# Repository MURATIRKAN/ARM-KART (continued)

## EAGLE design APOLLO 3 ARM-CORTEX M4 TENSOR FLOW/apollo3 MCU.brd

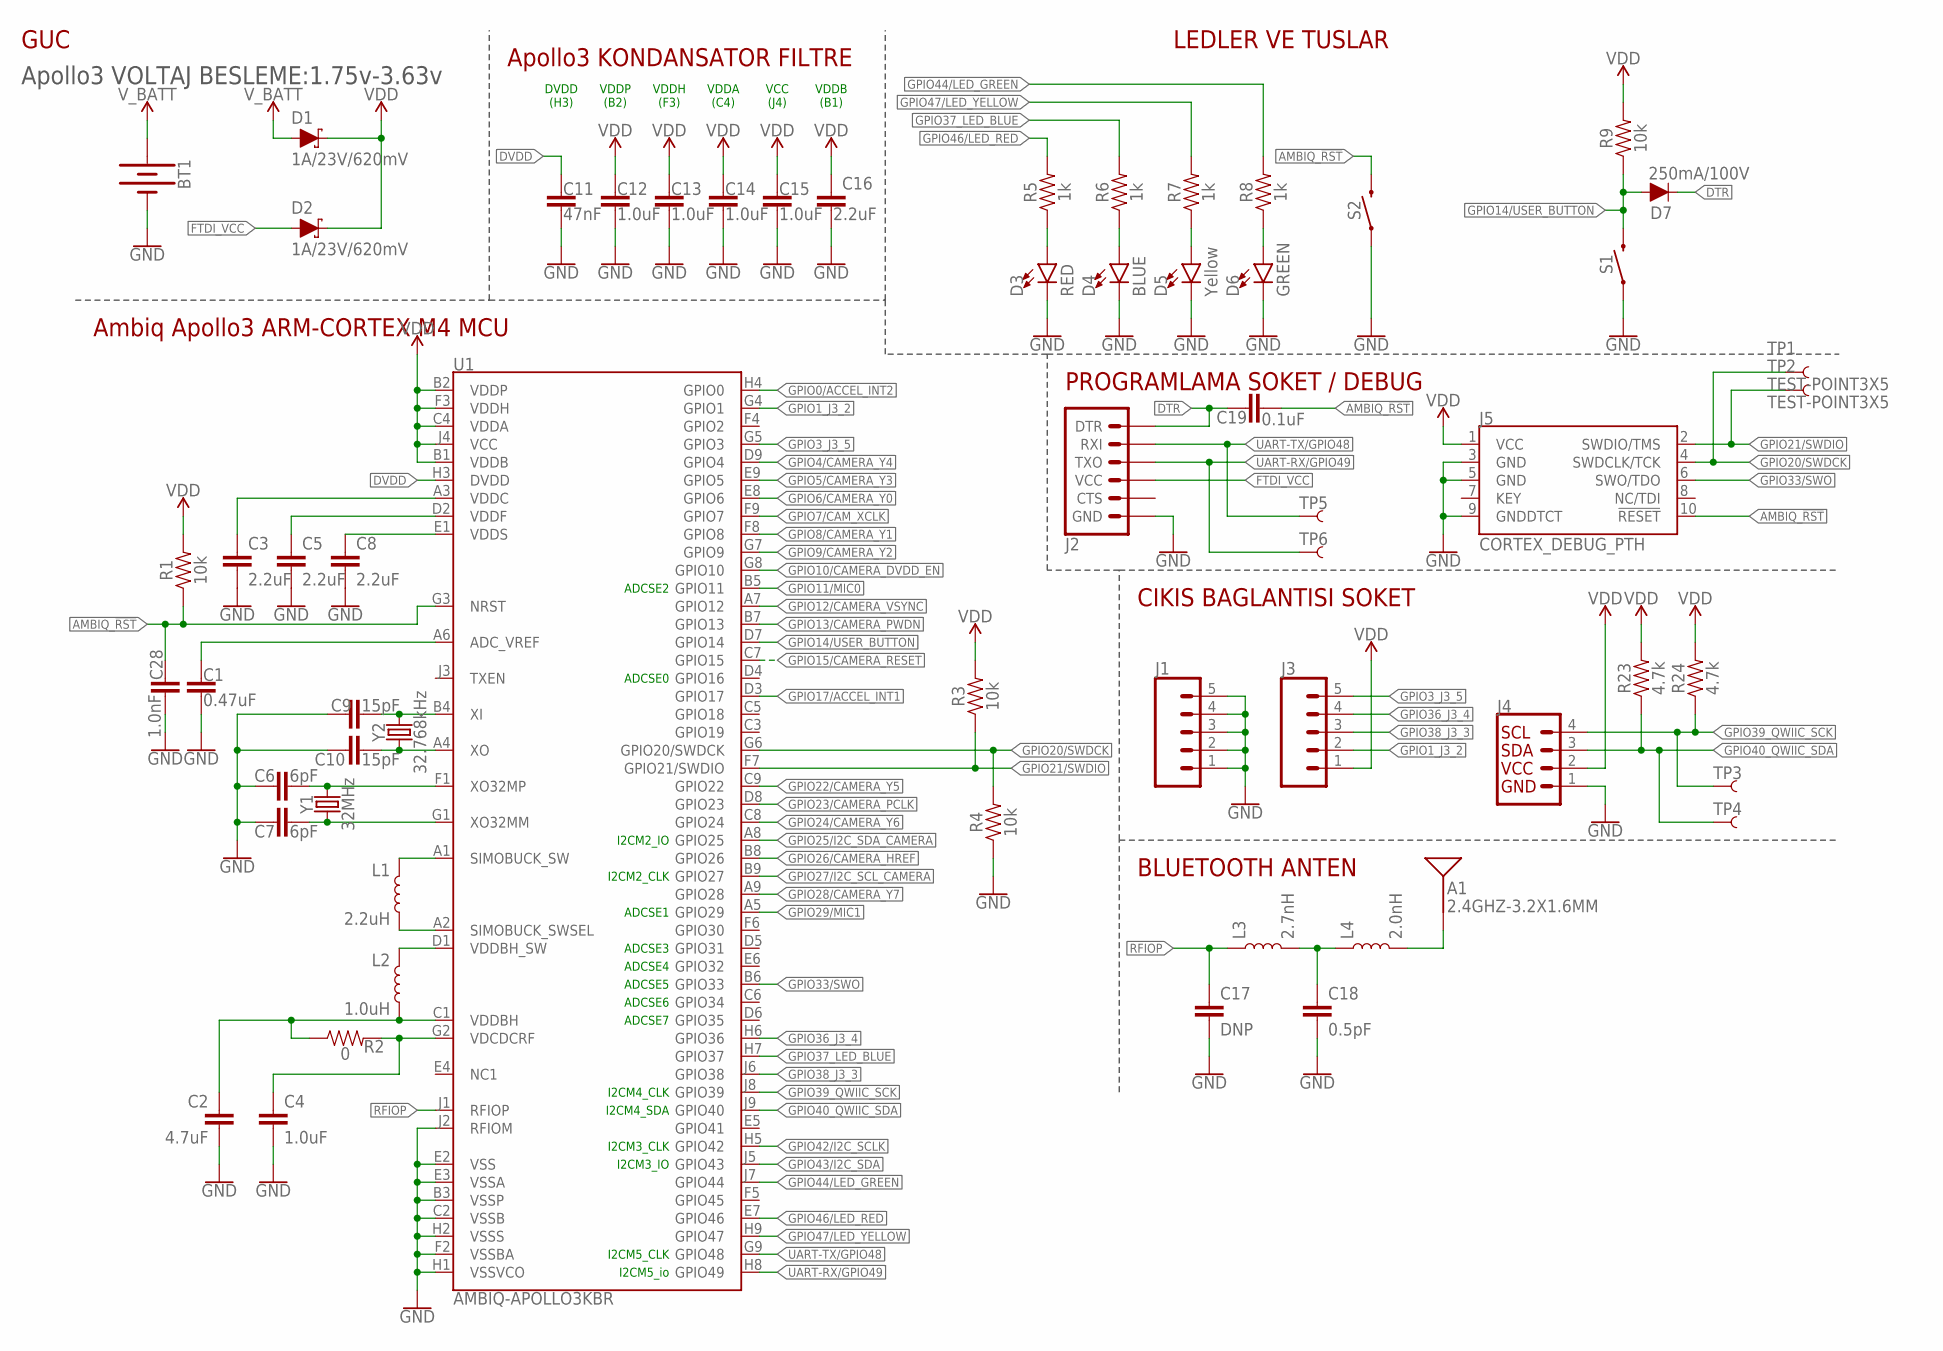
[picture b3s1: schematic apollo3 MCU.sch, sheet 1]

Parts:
A1: 2.4GHZ-3.2X1.6MM; ANT-2.4GHZ-3.2X1.6X1.2MM
BT1: BATTERY-20MM_SMD_4LEGS_OVERPASTE_INNER; BATTCON_20MM_4LEGS_OVERPASTE_INNER
C1: 0.47uF; 0402-TIGHT
C2: 4.7uF; 0402-TIGHT
C3, C5, C8, C16: 2.2uF; 0402-TIGHT
C4, C12, C13, C14, C15: 1.0uF; 0402-TIGHT
C6, C7: 6pF; 0402-TIGHT
C9, C10: 15pF; 0402-TIGHT
C11: 47nF; 0402-TIGHT
C17: DNP; 0402-TIGHT
C18: 0.5pF; 0402-TIGHT
C19: 0.1uF; 0402-TIGHT
C28: 1.0nF; 0402-TIGHT
D1, D2: 1A/23V/620mV; SOD-323@1
D3: RED; LED-0603
D4: BLUE; LED-0603
D5: Yellow; LED-0603
D6: GREEN; LED-0603
D7: 250mA/100V; SOD-323
J1, J3: CONN_05NO_SILK; 1X05_NO_SILK
J2: 6_PIN_SERIAL_TARGETSMD; 1X06-SMD_RA_MALE
J4: QWIIC_CONNECTORJS-1MM; 1X04_1MM_RA
J5: CORTEX_DEBUG_PTH; 2X5-PTH-1.27MM
L1: 2.2uH; 0805-WIDE
L2: 1.0uH; 0805-WIDE
L3: 2.7nH; 0402-TIGHT
L4: 2.0nH; 0402-TIGHT
R1, R3, R4, R9: 10k; 0402-TIGHT
R2: 0; 0402-TIGHT
R5, R6, R7, R8: 1k; 0603
R23, R24: 4.7k; 0603
S1, S2: MOMENTARY-SWITCH-SPST-SMD-5.2-TALL-REDUNDANT; TACTILE_SWITCH_SMD_5.2MM
TP1, TP2, TP3, TP4, TP5, TP6: TEST-POINT3X5; PAD.03X.05
U1: AMBIQ-APOLLO3KBR; BGA-81-5X5MM
Y1: 32MHz; CRYSTAL-SMD-2.0X1.6MM
Y2: 32.768kHz; CRYSTAL-SMD-3.2X1.5MM

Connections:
ADC_VREF: C1.1, U1.A6 (ADC_VREF)
AMBIQ_!RST: C19.2, C28.1, J5.10 (!RESET), R1.1, S2.3 (2), S2.4 (2), U1.G3 (NRST)
DTR: C19.1, D7.C, J2.1 (DTR)
DVDD: C11.1, U1.H3 (DVDD)
FTDI_VCC: D2.A, J2.4 (VCC)
GND: BT1.2 (-), C1.2, C2.2, C3.2, C4.2, C5.2, C6.1, C7.1, C8.2, C9.1, C10.1, C11.2, C12.2, C13.2, C14.2, C15.2, C16.2, C17.2, C18.2, C28.2, D3.C, D4.C, D5.C, D6.C, J1.1, J1.2, J1.3, J1.4, J1.5, J2.6 (GND), J4.1, J5.3 (GND), J5.5 (GND), J5.9 (GNDDTCT), R4.1, S1.1, S1.2 (1), S2.1, S2.2 (1), U1.B3 (VSSP), U1.C2 (VSSB), U1.E2 (VSS), U1.E3 (VSSA), U1.F2 (VSSBA), U1.H1 (VSSVCO), U1.H2 (VSSS), U1.J2 (RFIOM); also elsewhere on the board
GPIO0/ACCEL_INT2: U1.H4 (GPIO0); also elsewhere on the board
GPIO1_J3_2: J3.2, U1.G4 (GPIO1)
GPIO3_J3_5: J3.5, U1.G5 (GPIO3)
GPIO4/CAMERA_Y4: U1.D9 (GPIO4); also elsewhere on the board
GPIO5/CAMERA_Y3: U1.E9 (GPIO5); also elsewhere on the board
GPIO6/CAMERA_Y0: U1.E8 (GPIO6); also elsewhere on the board
GPIO7/CAM_XCLK: U1.F9 (GPIO7); also elsewhere on the board
GPIO8/CAMERA_Y1: U1.F8 (GPIO8); also elsewhere on the board
GPIO9/CAMERA_Y2: U1.G7 (GPIO9); also elsewhere on the board
GPIO10/CAMERA_DVDD_EN: U1.G8 (GPIO10); also elsewhere on the board
GPIO11/MIC0: U1.B5 (GPIO11); also elsewhere on the board
GPIO12/CAMERA_VSYNC: U1.A7 (GPIO12); also elsewhere on the board
GPIO13/CAMERA_PWDN: U1.B7 (GPIO13); also elsewhere on the board
GPIO14/USER_BUTTON: D7.A, R9.1, S1.3 (2), S1.4 (2), U1.D7 (GPIO14)
GPIO15/CAMERA_RESET: U1.C7 (GPIO15); also elsewhere on the board
GPIO17/ACCEL_INT1: U1.D3 (GPIO17); also elsewhere on the board
GPIO20/SWDCK: J5.4 (SWDCLK/TCK), R4.2, TP1.P$1, U1.G6 (GPIO20/SWDCK)
GPIO21/SWDIO: J5.2 (SWDIO/TMS), R3.1, TP2.P$1, U1.F7 (GPIO21/SWDIO)
GPIO22/CAMERA_Y5: U1.C9 (GPIO22); also elsewhere on the board
GPIO23/CAMERA_PCLK: U1.D8 (GPIO23); also elsewhere on the board
GPIO24/CAMERA_Y6: U1.C8 (GPIO24); also elsewhere on the board
GPIO25/I2C_SDA_CAMERA: U1.A8 (GPIO25); also elsewhere on the board
GPIO26/CAMERA_HREF: U1.B8 (GPIO26); also elsewhere on the board
GPIO27/I2C_SCL_CAMERA: U1.B9 (GPIO27); also elsewhere on the board
GPIO28/CAMERA_Y7: U1.A9 (GPIO28); also elsewhere on the board
GPIO29/MIC1: U1.A5 (GPIO29); also elsewhere on the board
GPIO33/SWO: J5.6 (SWO/TDO), U1.B6 (GPIO33)
GPIO36_J3_4: J3.4, U1.H6 (GPIO36)
GPIO37_LED_BLUE: R6.2, U1.H7 (GPIO37)
GPIO38_J3_3: J3.3, U1.J6 (GPIO38)
GPIO39_QWIIC_SCK: J4.4, R24.1, TP3.P$1, U1.J8 (GPIO39)
GPIO40_QWIIC_SDA: J4.3, R23.1, TP4.P$1, U1.J9 (GPIO40)
GPIO42/I2C_SCLK: U1.H5 (GPIO42); also elsewhere on the board
GPIO43/I2C_SDA: U1.J5 (GPIO43); also elsewhere on the board
GPIO44/LED_GREEN: R8.2, U1.J7 (GPIO44)
GPIO46/LED_RED: R5.2, U1.E7 (GPIO46)
GPIO47/LED_YELLOW: R7.2, U1.H9 (GPIO47)
unnamed: A1.FEED, L4.2
unnamed: C7.2, U1.G1 (XO32MM), Y1.1
unnamed: C6.2, U1.F1 (XO32MP), Y1.3 (2)
unnamed: D4.A, R6.1
unnamed: D3.A, R5.1
unnamed: D5.A, R7.1
unnamed: D6.A, R8.1
unnamed: C18.1, L3.2, L4.1
RFIOP: C17.1, L3.1, U1.J1 (RFIOP)
SIMBUCK_SWSEL: L1.2, U1.A2 (SIMOBUCK_SWSEL)
SIMOBUCK_SW: L1.1, U1.A1 (SIMOBUCK_SW)
UART-RX/GPIO49: J2.3 (TXO), TP6.P$1, U1.H8 (GPIO49)
UART-TX/GPIO48: J2.2 (RXI), TP5.P$1, U1.G9 (GPIO48)
VDCDCRF: C4.1, R2.2, U1.G2 (VDCDCRF)
VDD: C12.1, C13.1, C14.1, C15.1, C16.1, D1.C, D2.C, J3.1, J4.2, J5.1 (VCC), R1.2, R3.2, R9.2, R23.2, R24.2, U1.B1 (VDDB), U1.B2 (VDDP), U1.C4 (VDDA), U1.F3 (VDDH), U1.J4 (VCC); also elsewhere on the board
VDDBH: C2.1, L2.2, R2.1, U1.C1 (VDDBH)
VDDBH_SW: L2.1, U1.D1 (VDDBH_SW)
VDDC: C3.1, U1.A3 (VDDC)
VDDF: C5.1, U1.D2 (VDDF)
VDDS: C8.1, U1.E1 (VDDS)
V_BATT: BT1.1 (+), D1.A
X0: C10.2, U1.A4 (XO), Y2.P$1 (1)
XI: C9.2, U1.B4 (XI), Y2.P$2 (2)

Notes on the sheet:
DVDD (H3)
VDDP (B2)
VDDH (F3)
VDDA (C4)
VCC (J4)
VDDB (B1)
ADCSE0
ADCSE1
ADCSE2
ADCSE3
I2CM2_IO
I2CM2_CLK
I2CM4_CLK
I2CM4_SDA
I2CM3_CLK
I2CM3_IO
I2CM5_CLK
I2CM5_io
ADCSE6
ADCSE4
ADCSE5
ADCSE7
Apollo3 VOLTAJ BESLEME:1.75v-3.63v
Ambiq Apollo3 ARM-CORTEX M4 MCU
GUC
Apollo3 KONDANSATOR FILTRE
LEDLER VE TUSLAR
PROGRAMLAMA SOKET / DEBUG
CIKIS BAGLANTISI SOKET
BLUETOOTH ANTEN

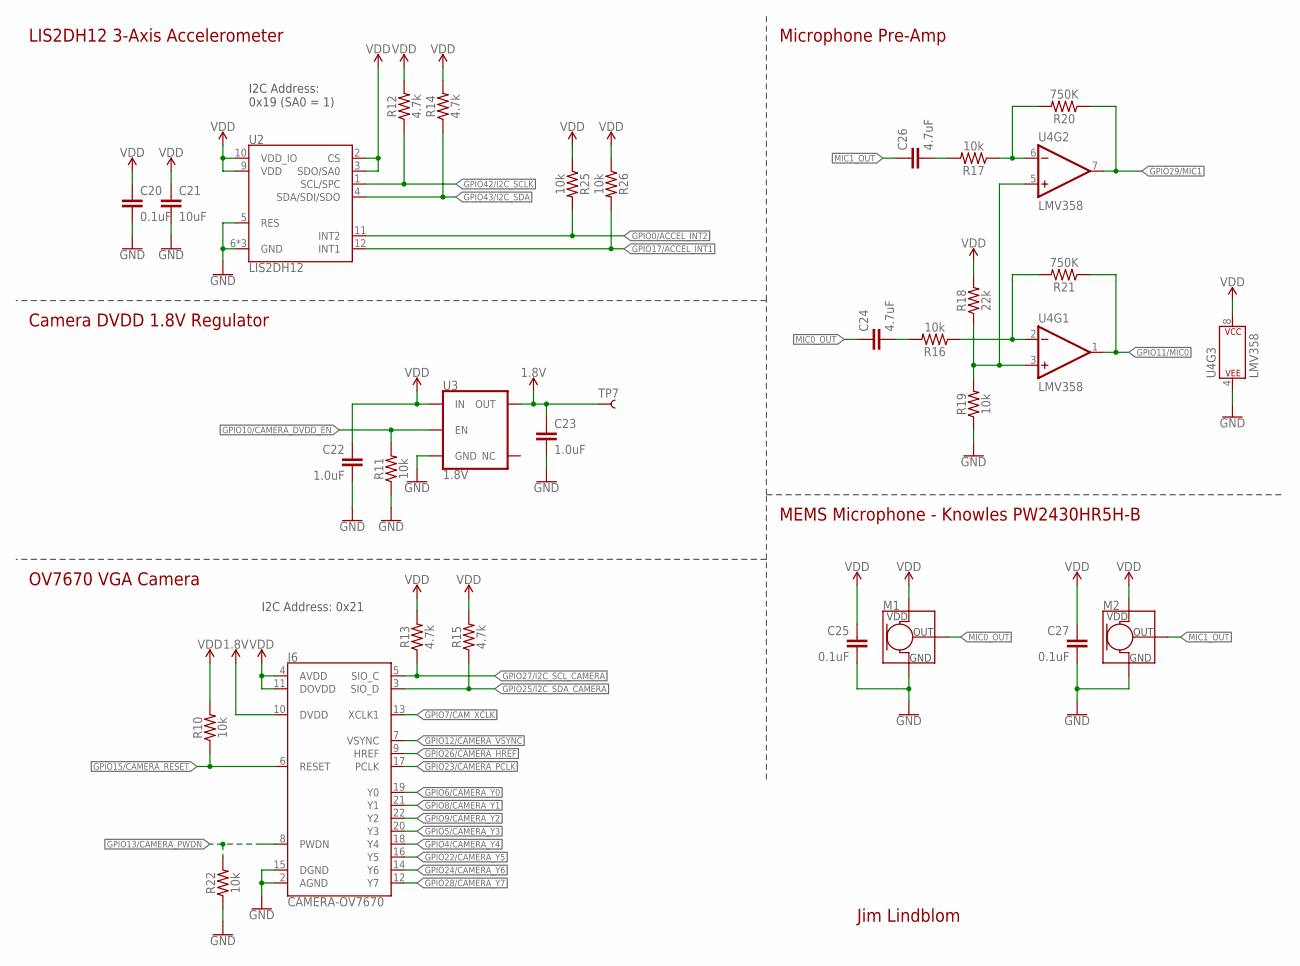
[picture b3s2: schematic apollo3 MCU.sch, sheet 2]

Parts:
C20, C25, C27: 0.1uF; 0402-TIGHT
C21: 10uF; 0603
C22, C23: 1.0uF; 0402-TIGHT
C24, C26: 4.7uF; 0603
J6: CAMERA-OV7670; FPC-24-AMPHENOL-SFV24R-1STE1HLF
M1, M2: MEMS_MIC; SPW2430HR5H-B
R10, R11, R19, R22, R25, R26: 10k; 0402-TIGHT
R12, R13, R14, R15: 4.7k; 0603
R16, R17: 10k; 0603
R18: 22k; 0402-TIGHT
R20, R21: 750K; 0603
TP7: TEST-POINT3X5; PAD.03X.05
U2: LIS2DH12; LGA-12-LISDH12
U3: 1.8V; SOT23-5
U4: LMV358; SO08

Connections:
1.8V: C23.1, J6.10 (DVDD), TP7.P$1, U3.5 (OUT)
GND: C20.2, C21.2, C22.2, C23.2, C25.2, C27.2, J6.2 (AGND), J6.15 (DGND), M1.2 (GND), M1.3 (GND), M2.2 (GND), M2.3 (GND), R11.1, R19.1, R22.1, U2.5 (RES), U2.6 (GND), U2.7 (GND), U2.8 (GND), U3.2 (GND), U4.4 (P$V-); also elsewhere on the board
GPIO0/ACCEL_INT2: R25.2, U2.11 (INT2); also elsewhere on the board
GPIO4/CAMERA_Y4: J6.18 (Y4); also elsewhere on the board
GPIO5/CAMERA_Y3: J6.20 (Y3); also elsewhere on the board
GPIO6/CAMERA_Y0: J6.19 (Y0); also elsewhere on the board
GPIO7/CAM_XCLK: J6.13 (XCLK1); also elsewhere on the board
GPIO8/CAMERA_Y1: J6.21 (Y1); also elsewhere on the board
GPIO9/CAMERA_Y2: J6.22 (Y2); also elsewhere on the board
GPIO10/CAMERA_DVDD_EN: R11.2, U3.3 (EN); also elsewhere on the board
GPIO11/MIC0: R21.1, U4.1 (OUT); also elsewhere on the board
GPIO12/CAMERA_VSYNC: J6.7 (VSYNC); also elsewhere on the board
GPIO13/CAMERA_PWDN: J6.8 (PWDN), R22.2; also elsewhere on the board
GPIO15/CAMERA_RESET: J6.6 (RESET), R10.1; also elsewhere on the board
GPIO17/ACCEL_INT1: R26.2, U2.12 (INT1); also elsewhere on the board
GPIO22/CAMERA_Y5: J6.16 (Y5); also elsewhere on the board
GPIO23/CAMERA_PCLK: J6.17 (PCLK); also elsewhere on the board
GPIO24/CAMERA_Y6: J6.14 (Y6); also elsewhere on the board
GPIO25/I2C_SDA_CAMERA: J6.3 (SIO_D), R15.1; also elsewhere on the board
GPIO26/CAMERA_HREF: J6.9 (HREF); also elsewhere on the board
GPIO27/I2C_SCL_CAMERA: J6.5 (SIO_C), R13.1; also elsewhere on the board
GPIO28/CAMERA_Y7: J6.12 (Y7); also elsewhere on the board
GPIO29/MIC1: R20.1, U4.7 (OUT); also elsewhere on the board
GPIO42/I2C_SCLK: R12.1, U2.1 (SCL/SPC); also elsewhere on the board
GPIO43/I2C_SDA: R14.1, U2.4 (SDA/SDI/SDO); also elsewhere on the board
MIC0_OUT: C24.1, M1.1 (OUT)
MIC1_OUT: C26.1, M2.1 (OUT)
unnamed: R18.1, R19.2, U4.3 (+IN), U4.5 (+IN)
unnamed: C24.2, R16.2
unnamed: R17.1, R20.2, U4.6 (-IN)
unnamed: R16.1, R21.2, U4.2 (-IN)
unnamed: C26.2, R17.2
VDD: C20.1, C21.1, C22.1, C25.1, C27.1, J6.4 (AVDD), J6.11 (DOVDD), M1.4 (VDD), M2.4 (VDD), R10.2, R12.2, R13.2, R14.2, R15.2, R18.2, R25.1, R26.1, U2.2 (CS), U2.3 (SDO/SA0), U2.9 (VDD), U2.10 (VDD_IO), U3.1 (IN), U4.8 (P$V+); also elsewhere on the board

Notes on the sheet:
Camera DVDD 1.8V Regulator
LIS2DH12 3-Axis Accelerometer
Microphone Pre-Amp
Jim Lindblom
I2C Address: 0x19 (SA0 = 1)
I2C Address: 0x21
OV7670 VGA Camera
MEMS Microphone - Knowles PW2430HR5H-B

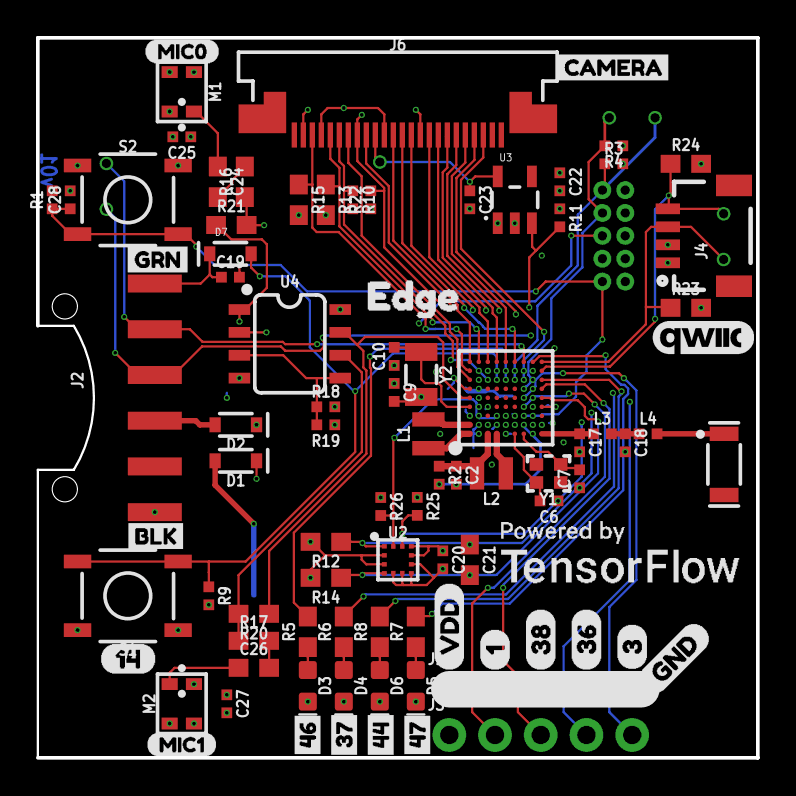
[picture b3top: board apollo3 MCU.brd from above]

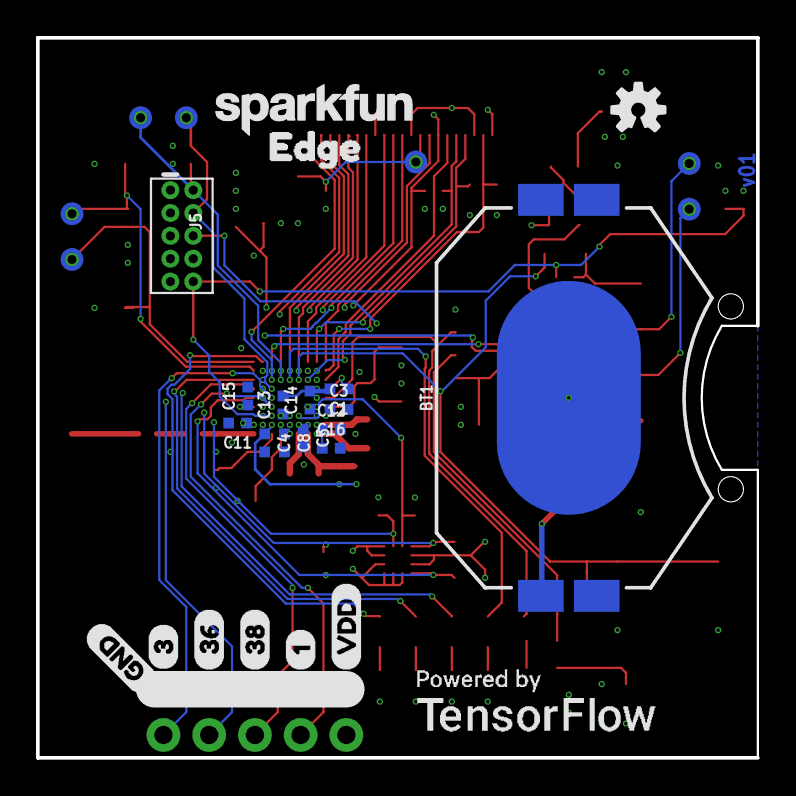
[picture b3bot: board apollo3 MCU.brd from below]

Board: 4 copper layers, 40.0 x 40.0 mm, 119 parts (30 on the bottom side), 74 nets.

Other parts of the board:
U$1: MIC00
U$2: BLK2
U$3, U$14: GND0
U$4, U$9: VDD1
U$5, U$8: 10
U$6, U$11: 383
U$7, U$12: 364
U$10, U$13: 31
U$15: 461
U$16: 372
U$17: 443
U$18: 470
U$19: QWIIC_COPYRIGHT_SMALL
U$20: CAMERA3
U$21, U$25: POWEREDBY_TF#JPG
U$22: MIC11
U$23, U$24: EDGE0
U$26: 1416
U$28: GRN1
U$29: SFE_LOGO_NAME_.1
U$30: OSHW-LOGO-S

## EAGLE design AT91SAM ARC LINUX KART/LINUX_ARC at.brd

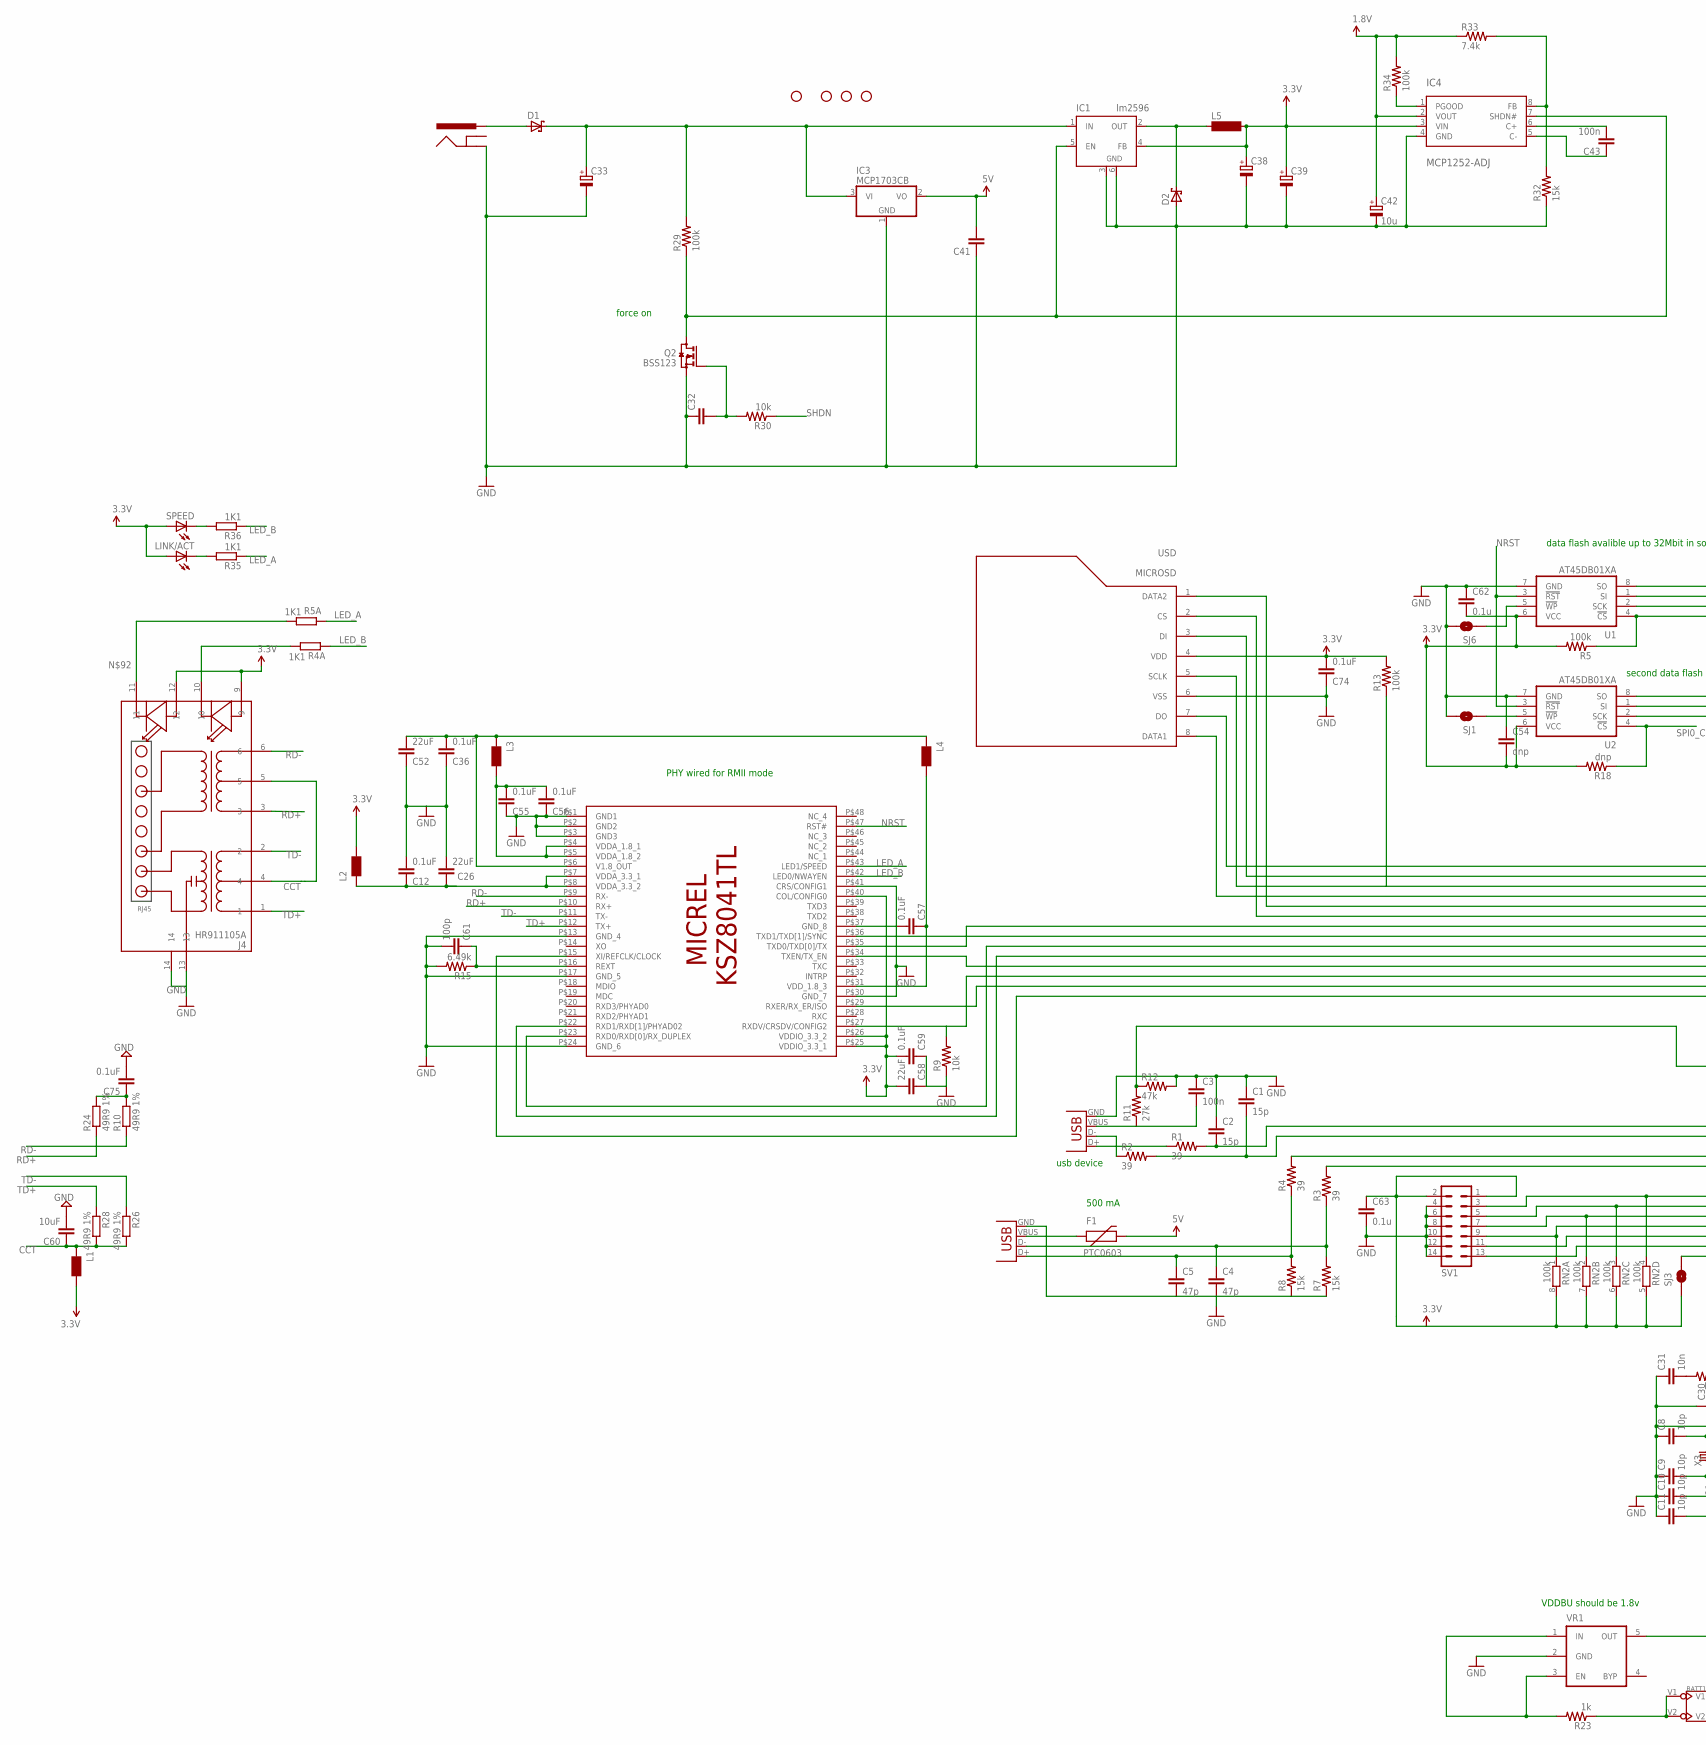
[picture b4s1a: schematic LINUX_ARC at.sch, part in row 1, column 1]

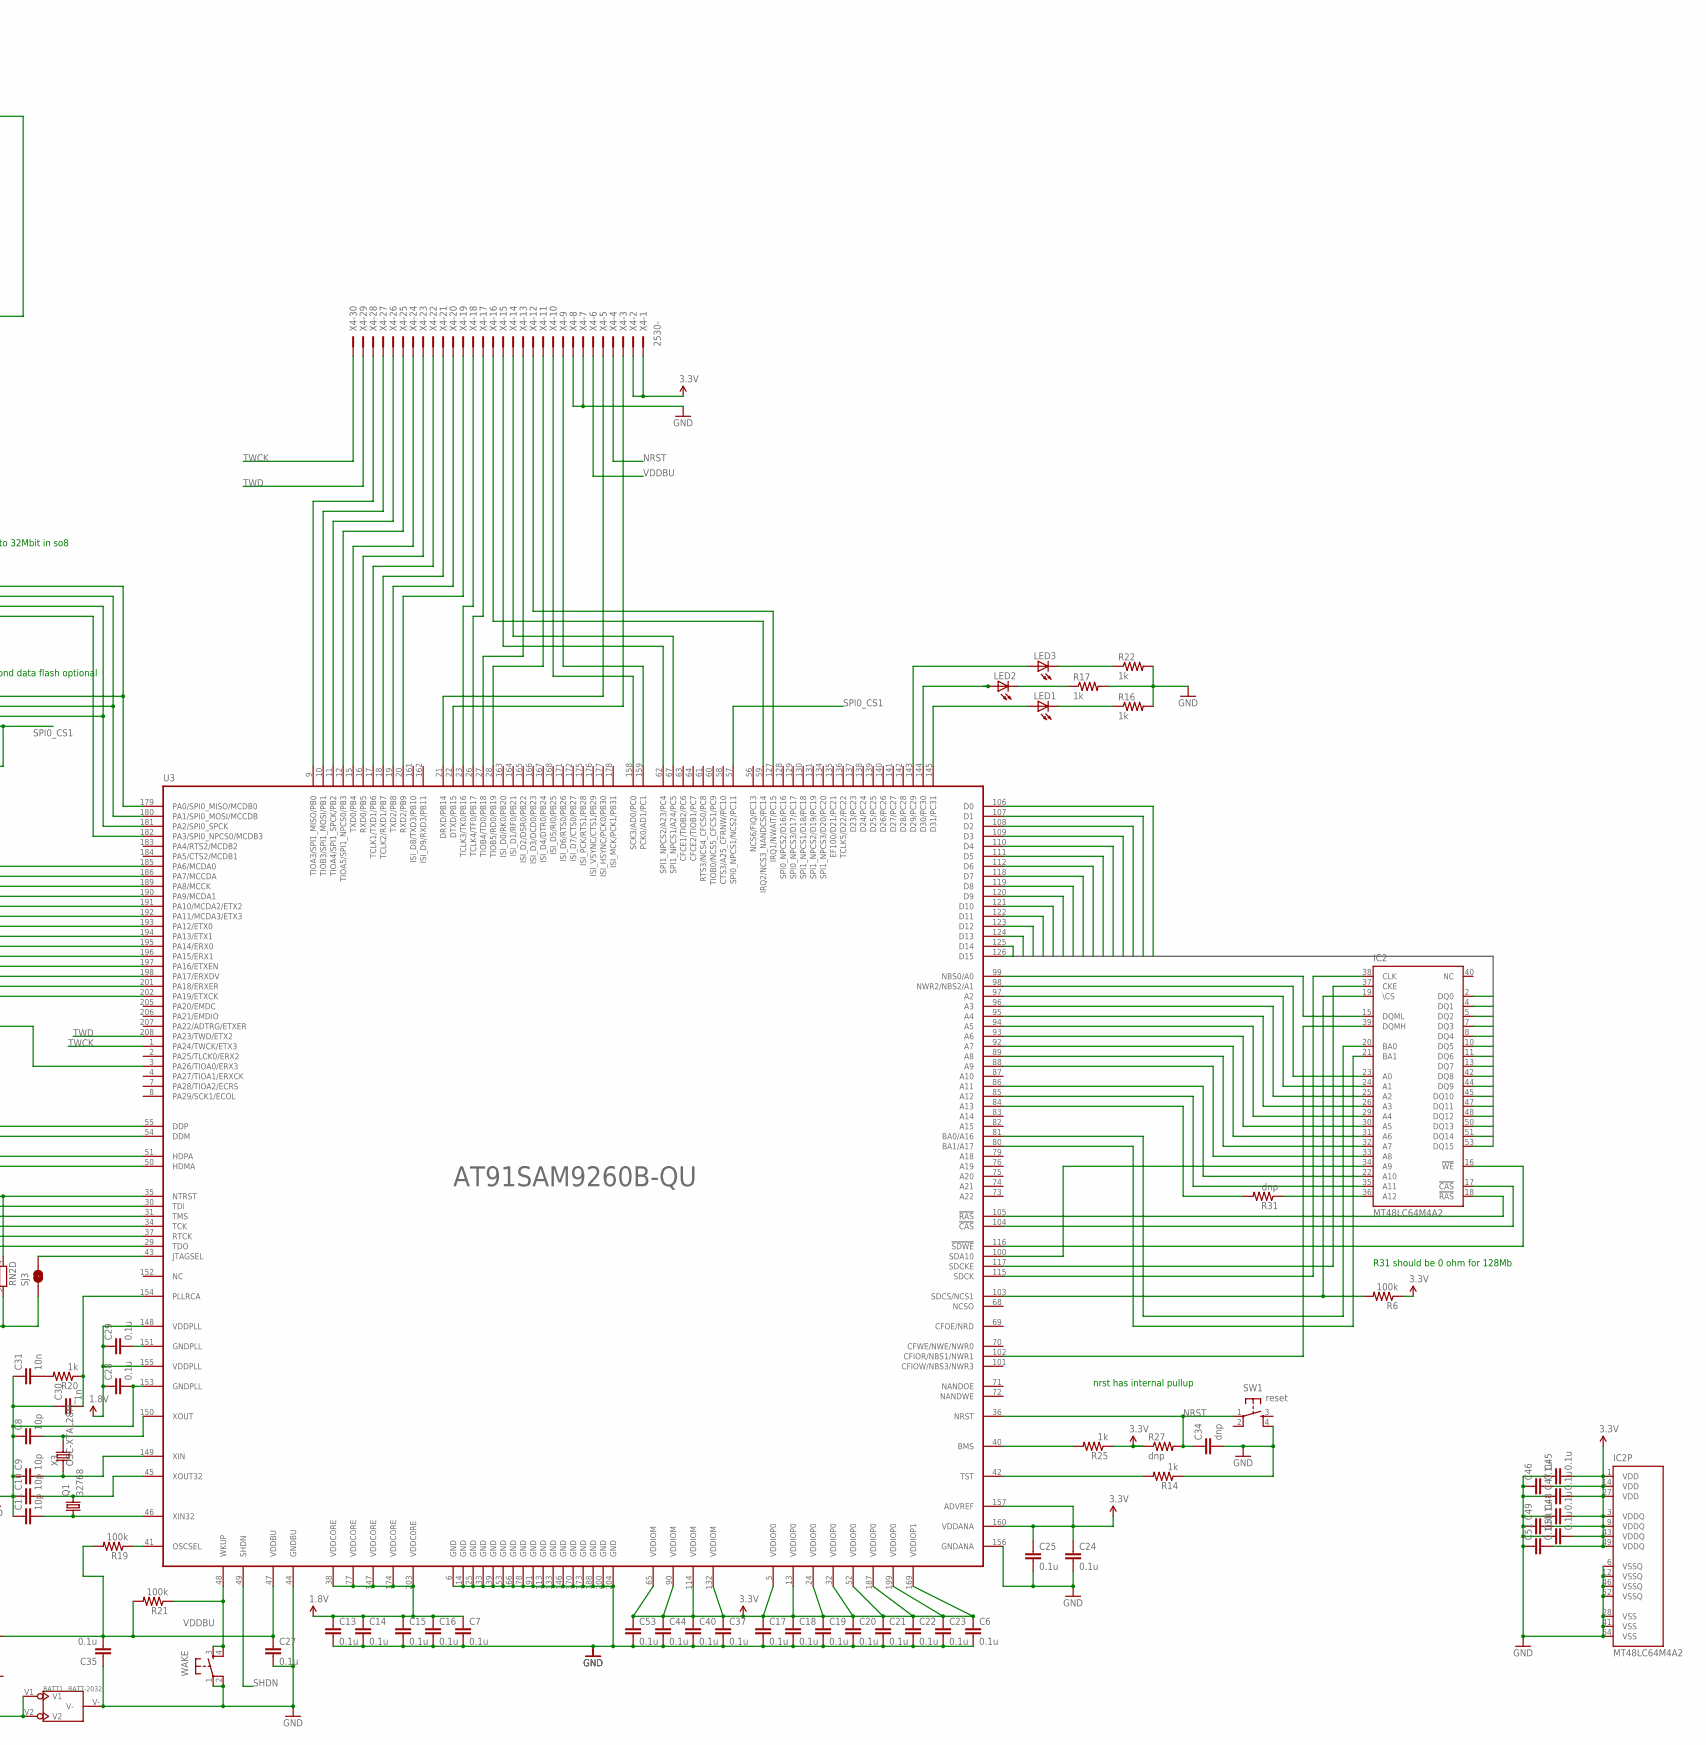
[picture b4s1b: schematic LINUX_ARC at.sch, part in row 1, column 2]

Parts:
BATT1: BATT-2032; 2032
C1, C2: 15p; 0603-CAP
C3: 100n; 0603-CAP
C4, C5: 47p; 0603-CAP
C6, C7, C13, C14, C15, C16, C17, C18, C19, C20, C21, C22, C23, C24, C25, C27, C28, C29, C35, C37, C40, C44, C45, C46, C47, C48, C49, C50, C51, C53, C62, C63: 0.1u; 0603-CAP
C8, C9, C10, C11: 10p; 0603-CAP
C12, C36, C55, C56, C57, C59, C74, C75: 0.1uF; C0603
C26, C52, C58: 22uF; C0603
C30: 1n; 0603-CAP
C31: 10n; 0603-CAP
C32, C41: CAPC603; C603
C33, C39: CAP_POLSMC_B; SMC_B
C34, C54: dnp; 0603-CAP
C38: CAP_POLCASE_A; CASE_A
C42: 10u; SMC_B
C43: 100n; C603
C60: 10uF; C0603
C61: 100p; C0603
D1, D2: SCHOTTKY-DIODESMD; SMB
F1: PTC0603; 0603
IC1: lm2596; TO263-5
IC2: MT48LC64M4A2; TSOP54-400
IC3: MCP1703CB; SOT23
IC4: MCP1252-ADJ; MSOP8
J4: HR911105A
JP1, JP2, JP3, JP4: STAND-OFF
L1, L2, L3, L4: WE-KIL_0805; WE-KI_0805_B
L5: MS85
LED1, LED2, LED3: LEDCHIPLED_0805; CHIPLED_0805
LINK/ACT: LEDCHIPLED_0805; CHIPLED_0805
Q1: 32768; TC26H
Q2: BSS123; SOT23
R1, R2, R3, R4: 39; R0603
R4A, R5A, R35, R36: 1K1; R0603
R5, R6, R13, R19, R21, R29, R34: 100k; R0603
R7, R8, R32: 15k; R0603
R9, R30: 10k; R0603
R10, R24, R26, R28: 49R9 1%; R0603
R11: 27k; R0603
R12: 47k; R0603
R14, R16, R17, R20, R22, R23, R25: 1k; R0603
R15: 6.49k; R0603
R18, R27, R31: dnp; R0603
R33: 7.4k; R0603
RN2: 100k; RN8P-4R-CRA06S
SJ1, SJ3, SJ6: SOLDERJUMPERNO; SJ_2S-NO
SPEED: LEDCHIPLED_0805; CHIPLED_0805
SV1: MA07-2
SW1: reset; TACT_SWITCH_SMALL
U1, U2: AT45DB01XA; SO08W
U3: AT91SAM9260B-QU; PQFP208
U$1: KSZ8041TL; 48PIN-TQFN
U$2: POWER_JACKSMD; POWER_JACK_SMD
USD: MICROSD
VR1: MIC5205; SOT-23-5
WAKE: SW-SMD-SMALL; TACT_SWITCH_SMALL
X1: USB-MB-S
X2: USB-A-H
X3: OSC-XTAL28M_; 5X8
X4: 2530-; PAK100/2500-30

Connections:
1.8V: C7.1, C13.1, C14.1, C15.1, C16.1, C28.1, C29.1, C42.+, R33.1, R34.2, U3.38 (VDDCORE), U3.77 (VDDCORE), U3.147 (VDDCORE), U3.148 (VDDPLL), U3.155 (VDDPLL), U3.174 (VDDCORE), U3.203 (VDDC0RE)
3.3V: C6.1, C17.1, C18.1, C19.1, C20.1, C21.1, C22.1, C23.1, C24.1, C25.1, C37.1, C38.+, C39.+, C40.1, C44.1, C45.2, C46.2, C47.2, C48.2, C49.2, C50.2, C51.2, C53.1, C54.2, C58.1, C59.1, C62.2, C63.1, C74.1, IC1.4 (FB), IC2.1 (VDD), IC2.3 (VDDQ), IC2.9 (VDDQ), IC2.14 (VDD), IC2.27 (VDD), IC2.43 (VDDQ), IC2.49 (VDDQ), IC4.3 (VIN), J4.9, J4.12, L1.1 (2), L2.1 (2), L5.2, LINK/ACT.A, R5.2, R6.1, R13.2, R18.2, R25.1, R27.1, RN2.5 (2), RN2.6 (2), RN2.7 (2), RN2.8 (2), SJ3.1, SPEED.A, SV1.1, SV1.2, U1.6 (VCC), U2.6 (VCC), U3.5 (VDDIOP0), U3.13 (VDDIOP0), U3.24 (VDDIOP0), U3.32 (VDDIOP0), U3.52 (VDDIOP0), U3.65 (VDDIOM), U3.90 (VDDIOM), U3.114 (VDDIOM), U3.132 (VDDIOM), U3.157 (ADVREF), U3.160 (VDDANA), U3.169 (VDDIOP1), U3.187 (VDDIOP0), U3.199 (VDDIOP0), U$1.P$25 (VDDIO_3.3_1), U$1.P$26 (VDDIO_3.3_2), U$1.P$40 (COL/CONFIG0), USD.4 (VDD), X4.1, X4.2
5V: C41.2, F1.2, IC3.2 (VO)
CCT: C60.1, J4.4, J4.5, L1.2 (1), R26.2, R28.2
D0: IC2.2 (DQ0), U3.106 (D0)
D1: IC2.4 (DQ1), U3.107 (D1)
D2: IC2.5 (DQ2), U3.108 (D2)
D3: IC2.7 (DQ3), U3.109 (D3)
D4: IC2.8 (DQ4), U3.110 (D4)
D5: IC2.10 (DQ5), U3.111 (D5)
D6: IC2.11 (DQ6), U3.112 (D6)
D7: IC2.13 (DQ7), U3.118 (D7)
D8: IC2.42 (DQ8), U3.119 (D8)
D9: IC2.44 (DQ9), U3.120 (D9)
D10: IC2.45 (DQ10), U3.121 (D10)
D11: IC2.47 (DQ11), U3.122 (D11)
D12: IC2.48 (DQ12), U3.123 (D12)
D13: IC2.50 (DQ13), U3.124 (D13)
D14: IC2.51 (DQ14), U3.125 (D14)
D15: IC2.53 (DQ15), U3.126 (D15)
GND: BATT1.V-, C1.1, C2.1, C3.1, C4.2, C5.2, C6.2, C7.2, C8.1, C9.1, C10.1, C11.1, C12.1, C13.2, C14.2, C15.2, C16.2, C17.2, C18.2, C19.2, C20.2, C21.2, C22.2, C23.2, C24.2, C25.2, C26.1, C27.2, C28.2, C30.1, C31.1, C32.1, C33.-, C34.2, C35.1, C36.2, C37.2, C38.-, C39.-, C40.2, C41.1, C42.-, C44.2, C45.1, C46.1, C47.1, C48.1, C49.1, C50.1, C51.1, C52.2, C53.2, C54.1, C55.2, C56.2, C57.1, C58.2, C59.2, C60.2, C61.1, C62.1, C63.2, C74.2, C75.2, D2.A, IC1.3 (GND), IC1.6 (GND), IC2.6 (VSSQ), IC2.12 (VSSQ), IC2.28 (VSS), IC2.41 (VSS), IC2.46 (VSSQ), IC2.52 (VSSQ), IC2.54 (VSS), IC3.1 (GND), IC4.4 (GND), J4.13, J4.14, Q2.2 (S), R7.1, R8.1, R9.1, R12.2, R14.1, R15.2, R16.2, R17.2, R22.2, R32.1, SJ1.2, SJ6.2, SV1.4, SV1.6, SV1.8, SV1.10, SV1.12, SV1.14, SW1.4, U1.7 (GND), U2.7 (GND), U3.6 (GND), U3.14 (GND), U3.25 (GND), U3.33 (GND), U3.39 (GND), U3.44 (GNDBU), U3.53 (GND), U3.66 (GND), U3.78 (GND), U3.91 (GND), U3.113 (GND), U3.133 (GND), U3.146 (GND), U3.153 (GNDPLL), U3.156 (GNDANA), U3.170 (GND), U3.173 (GND), U3.188 (GND), U3.200 (GND), U3.204 (GND), U$1.P$1 (GND1), U$1.P$2 (GND2), U$1.P$3 (GND3), U$1.P$13 (GND_4), U$1.P$17 (GND_5), U$1.P$24 (GND_6), U$1.P$30 (GND_7), U$1.P$37 (GND_8), U$1.P$41 (CRS/CONFIG1), U$2.P$4 (GND), USD.6 (VSS), VR1.2 (GND), WAKE.1, WAKE.2, X1.GND, X2.GND, X4.7, X4.8
LED_A: R5A.1, R35.1, U$1.P$43 (LED1/SPEED)
LED_B: R4A.1, R36.1, U$1.P$42 (LED0/NWAYEN)
LED_SPEED: J4.10, R4A.2
unnamed: RN2.4 (1), SV1.3, U3.35 (NTRST)
unnamed: C10.2, Q1.2, U3.45 (XOUT32)
unnamed: C11.2, Q1.1, U3.46 (XIN32)
unnamed: C9.2, U3.149 (XIN), X3.1 (X1)
unnamed: C8.2, U3.150 (XOUT), X3.2 (X2)
unnamed: C29.2, U3.151 (GNDPLL)
unnamed: IC2.18 (!RAS), U3.105 (!RAS)
unnamed: IC2.17 (!CAS), U3.104 (!CAS)
unnamed: IC2.16 (!WE), U3.116 (!SDWE)
unnamed: IC2.15 (DQML), U3.99 (NBS0/A0)
unnamed: IC2.23 (A0), U3.98 (NWR2/NBS2/A1)
unnamed: IC2.24 (A1), U3.97 (A2)
unnamed: IC2.20 (BA0), U3.81 (BA0/A16)
unnamed: IC2.21 (BA1), U3.80 (BA1/A17)
unnamed: IC2.38 (CLK), U3.115 (SDCK)
unnamed: IC2.25 (A2), U3.96 (A3)
unnamed: IC2.26 (A3), U3.95 (A4)
unnamed: C4.1, R3.1, R7.2, U3.191 (PA10/MCDA2/ETX2), USD.1 (DATA2), X2.D-
unnamed: C5.1, R4.1, R8.2, X2.D+
unnamed: R4.2, U3.51 (HDPA)
unnamed: SJ3.2, U3.43 (JTAGSEL)
unnamed: R3.2, U3.50 (HDMA)
unnamed: U1.2 (SCK), U2.2 (SCK), U3.181 (PA2/SPI0_SPCK)
unnamed: IC1.5 (EN), IC4.7 (SHDN#), Q2.3 (D), R29.1
unnamed: U1.1 (SI), U2.1 (SI), U3.180 (PA1/SPI0_MOSI/MCCDB)
unnamed: C61.2, R15.1, U$1.P$16 (REXT)
unnamed: U3.23 (TCLK3/TK0/PB16), X4.18
unnamed: U3.26 (TCLK4/TF0/PB17), X4.17
unnamed: U1.8 (SO), U2.8 (SO), U3.179 (PA0/SPI0_MISO/MCDB0)
unnamed: U3.9 (TIOA3/SPI1_MISO/PB0), X4.28
unnamed: SV1.11, U3.37 (RTCK)
unnamed: RN2.3 (1), SV1.5, U3.30 (TDI)
unnamed: RN2.2 (1), SV1.7, U3.31 (TMS)
unnamed: RN2.1, SV1.9, U3.34 (TCK)
unnamed: SJ1.1, U2.5 (!WP!)
unnamed: U3.27 (TIOB4/TD0/PB18), X4.13
unnamed: IC2.29 (A4), U3.94 (A5)
unnamed: IC2.30 (A5), U3.93 (A6)
unnamed: IC2.31 (A6), U3.92 (A7)
unnamed: IC2.32 (A7), U3.89 (A8)
unnamed: IC2.33 (A8), U3.88 (A9)
unnamed: IC2.34 (A9), U3.100 (SDA10)
unnamed: IC2.22 (A10), U3.86 (A11)
unnamed: IC2.35 (A11), U3.85 (A12)
unnamed: R31.2, U3.84 (A13)
unnamed: IC2.36 (A12), R31.1
unnamed: R19.1, U3.41 (OSCSEL)
unnamed: R5.1, U1.4 (!CS!), U3.182 (PA3/SPI0_NPCS0/MCDB3)
unnamed: U3.28 (TIOB5/RD0/PB19), X4.11
unnamed: C75.1, R10.2, R24.2
unnamed: C12.2, C26.2, L2.2 (1), U$1.P$7 (VDDA_3.3_1), U$1.P$8 (VDDA_3.3_2)
unnamed: C32.2, Q2.1 (G), R30.2
unnamed: U3.202 (PA19/ETXCK), U$1.P$15 (XI/REFCLK/CLOCK)
unnamed: R9.2, U3.198 (PA17/ERXDV), U$1.P$27 (RXDV/CRSDV/CONFIG2)
unnamed: IC2.39 (DQMH), U3.102 (CFIOR/NBS1/NWR1)
unnamed: U3.195 (PA14/ERX0), U$1.P$23 (RXD0/RXD[0]/RX_DUPLEX)
unnamed: U3.196 (PA15/ERX1), U$1.P$22 (RXD1/RXD[1]/PHYAD02)
unnamed: U3.201 (PA18/ERXER), U$1.P$29 (RXER/RX_ER/ISO)
unnamed: SJ6.1, U1.5 (!WP!)
unnamed: U3.197 (PA16/ETXEN), U$1.P$34 (TXEN/TX_EN)
unnamed: U3.193 (PA12/ETX0), U$1.P$35 (TXD0/TXD[0]/TX)
unnamed: U3.194 (PA13/ETX1), U$1.P$36 (TXD1/TXD[1]/SYNC)
unnamed: R25.2, U3.40 (BMS)
unnamed: LED3.A, U3.143 (D29/PC29)
unnamed: R36.2, SPEED.C
unnamed: U3.10 (TIOB3/SPI1_MOSI/PB1), X4.27
unnamed: R14.2, U3.42 (TST)
unnamed: IC2.19 (\CS), R6.2, U3.103 (SDCS/NCS1)
unnamed: IC2.37 (CKE), U3.117 (SDCKE)
unnamed: C55.1, C56.1, L3.1 (2), U$1.P$4 (VDDA_1.8_1), U$1.P$5 (VDDA_1.8_2)
unnamed: C57.2, L4.1 (2), U$1.P$31 (VDD_1.8_3)
unnamed: LINK/ACT.C, R35.2
unnamed: C36.1, C52.1, L3.2 (1), L4.2 (1), U$1.P$6 (V1.8_OUT)
unnamed: LED2.A, U3.144 (D30/PC30)
unnamed: R23.2, VR1.1 (IN), VR1.3 (EN)
unnamed: J4.11, R5A.2
unnamed: LED1.A, U3.145 (D31/PC31)
unnamed: LED1.C, R16.1
unnamed: C1.2, R2.2, U3.54 (DDM)
unnamed: C2.2, R1.2, U3.55 (DDP)
unnamed: LED2.C, R17.1
unnamed: R2.1, X1.D-
unnamed: R1.1, X1.D+
unnamed: LED3.C, R22.1
unnamed: C3.2, R11.1, X1.VBUS
unnamed: U3.11 (TIOA4/SPI1_SPCK/PB2), X4.26
unnamed: U3.12 (TIOA5/SPI1_NPCS0/PB3), X4.25
unnamed: C33.+, D1.C, IC1.1 (IN), IC3.3 (VI), R29.2
unnamed: BATT1.V1, BATT1.V2, R23.1
unnamed: U3.190 (PA9/MCDA1), USD.8 (DATA1)
unnamed: U3.15 (TXD0/PB4), X4.24
unnamed: U3.16 (RXD0/PB5), X4.23
unnamed: U3.17 (TCLK1/TXD1/PB6), X4.22
unnamed: U3.18 (TCLK2/RXD1/PB7), X4.21
unnamed: U3.19 (TXD2/PB8), X4.20
unnamed: U3.20 (RXD2/PB9), X4.19
unnamed: U3.158 (SCK3/AD0/PC0), X4.10
unnamed: U3.159 (PCK0/AD1/PC1), X4.9
unnamed: U3.21 (DRXD/PB14), X4.5
unnamed: U3.22 (DTXD/PB15), X4.3
unnamed: U3.62 (SPI1_NPCS2/A23/PC4), X4.15
unnamed: C31.2, R20.2
unnamed: C30.2, R20.1, U3.154 (PLLRCA)
unnamed: F1.1, X2.VBUS
unnamed: U3.67 (SPI1_NPCS1/A24/PC5), X4.14
unnamed: U3.59 (IRQ2/NCS3_NANDCS/PC14), X4.16
unnamed: U3.127 (IRQ1/NWAIT/PC15), X4.12
unnamed: SV1.13, U3.29 (TDO)
unnamed: D1.A, U$2.VIN0 (PWR)
unnamed: D2.C, IC1.2 (OUT), L5.1
unnamed: C43.2, IC4.6 (C+)
unnamed: C43.1, IC4.5 (C-)
unnamed: IC4.8 (FB), R32.2, R33.2
unnamed: IC4.1 (PGOOD), R34.1
unnamed: R21.1, U3.48 (WKUP), WAKE.3, WAKE.4
NRST: C34.1, R27.2, SW1.1, U1.3 (!RST!), U2.3 (!RST!), U3.36 (NRST), U$1.P$47 (RST#), X4.4
RD+: J4.3, R24.1, U$1.P$10 (RX+)
RD-: J4.6, R10.1, U$1.P$9 (RX-)
SDCLK: R13.1, U3.189 (PA8/MCCK), USD.5 (SCLK)
SDCS: U3.192 (PA11/MCDA3/ETX3), USD.2 (CS)
SDMISO: U3.185 (PA6/MCDA0), USD.7 (DO)
SDMOSI: U3.186 (PA7/MCCDA), USD.3 (DI)
SHDN: R30.1, U3.49 (SHDN)
SPI0_CS1: R18.1, U2.4 (!CS!), U3.57 (SPI0_NPCS1/NCS2/PC11)
TD+: J4.1, R28.1, U$1.P$12 (TX+)
TD-: J4.2, R26.1, U$1.P$11 (TX-)
TWCK: U3.1 (PA24/TWCK/ETX3), X4.30
TWD: U3.208 (PA23/TWD/ETX2), X4.29
USBDETECT: R11.2, R12.1, U3.3 (PA26/TIOA0/ERX3)
VDDBU: C27.1, C35.2, R19.2, R21.2, U3.47 (VDDBU), VR1.5 (OUT), X4.6

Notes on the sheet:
R31 should be 0 ohm for 128Mb
usb device
data flash avalible up to 32Mbit in so8
500 mA
PHY wired for RMII mode
VDDBU should be 1.8v
nrst has internal pullup
second data flash optional
force on

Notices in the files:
parts and their libraries:
SparkFun-Aesthetics: Licensing: Creative Commons ShareAlike 4.0 International - https://creativecommons.org/licenses/by-sa/4.0
microbuilder: This work is placed in the public domain, and may be freely used for commercial and non-commercial work with the following conditions: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
